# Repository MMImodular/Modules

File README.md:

# Modules
Repository for all my eurorack module designs

Each directory has its own ReadMe with information on each module

If you decide to get some of your own PCBs fabbed from these files, please consider shooting me a few bucks to help support future projects!

paypal.me/AboutBlank

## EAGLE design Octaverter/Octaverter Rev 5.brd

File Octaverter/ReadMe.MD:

# Octaverter

**Octaverter is currently in prototyping stages. The data here is to help beta testers with their builds. Nothing is guaranteed to work just yet.**

* 8 attenuverters in 12hp
* Each attenuverter is normalled to the one below it if no plug is inserted to its output
* Each input is normalled to 5V if no plug is inserted
* Each attenuverter has a gain of 1.5
* Bi-color LEDs to help visualize the output, red for negative, green for positive

Octaverter has been in the works for several months and has gone through a record number of revisions. This is 5th and hopefully last version of the module. Octaverter is a one-stop-shop for many functions beyond just attenuversion. It can be used as a mixer, offset generator, sidechain generator, amplifier, and even distortion.

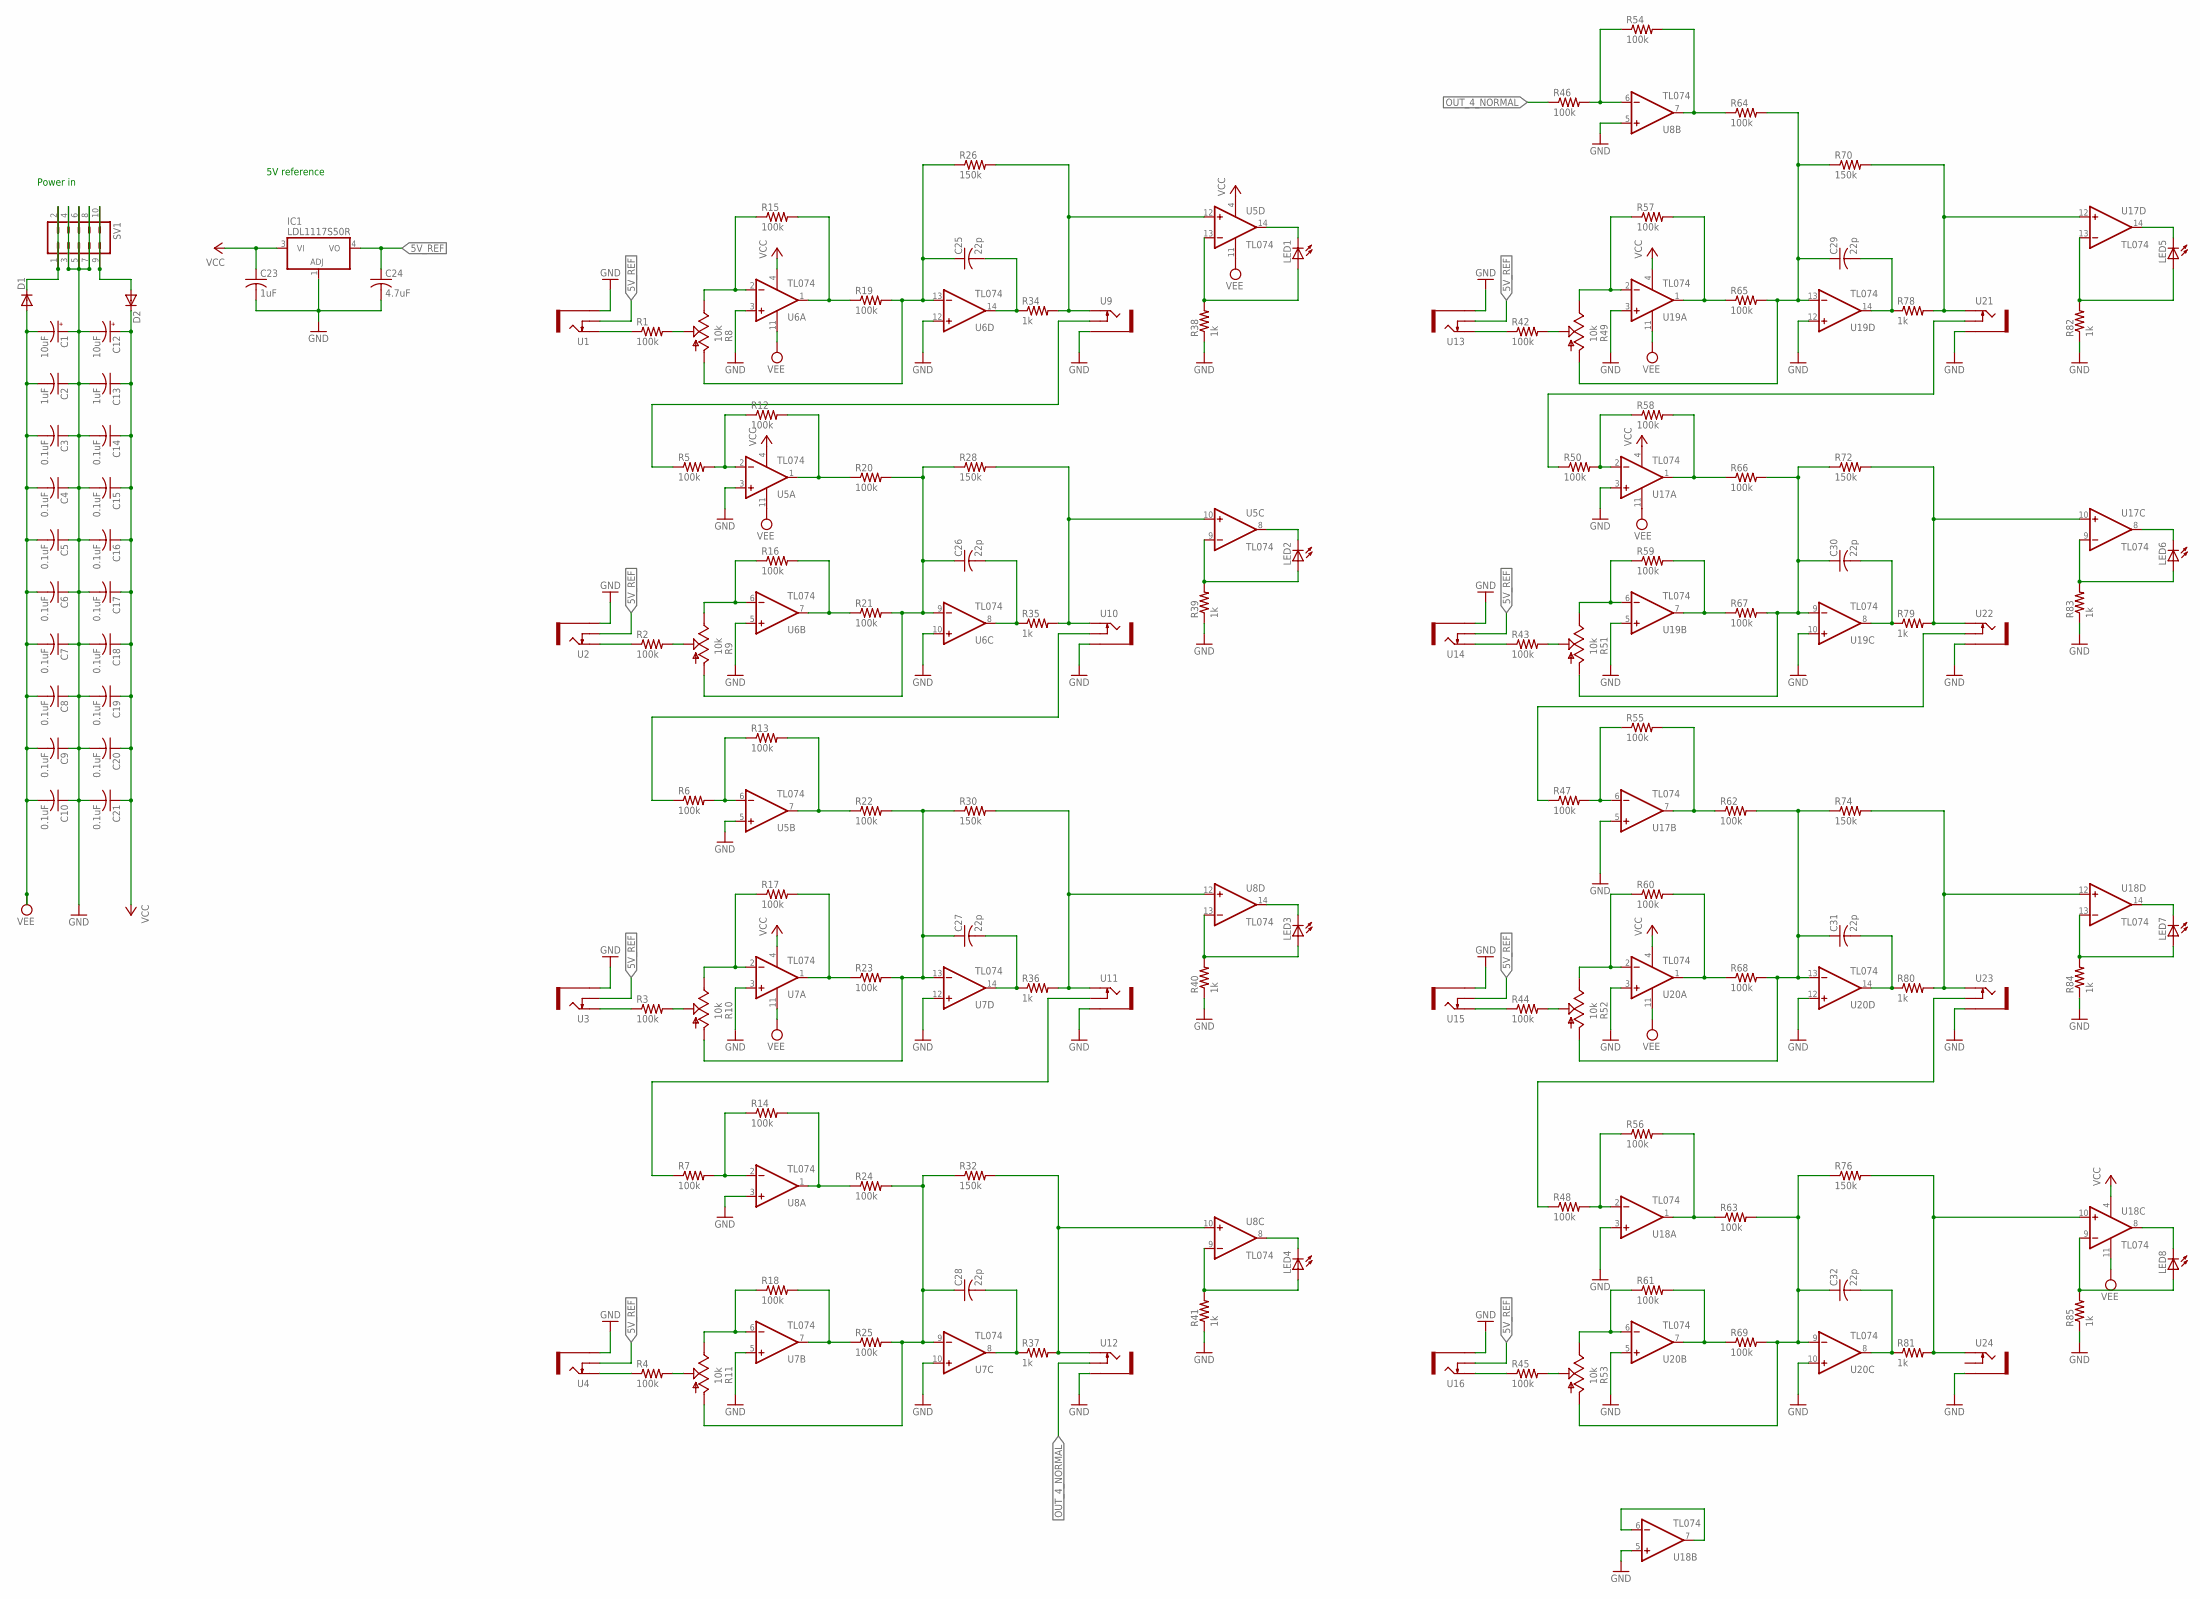
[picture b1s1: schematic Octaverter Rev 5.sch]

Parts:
C1, C12: 10uF; PANASONIC_B
C2, C13, C23: 1uF; C0603
C3, C4, C5, C6, C7, C8, C9, C10, C14, C15, C16, C17, C18, C19, C20, C21: 0.1uF; C0603
C24: 4.7uF; C0603
C25, C26, C27, C28, C29, C30, C31, C32: 22p; C0603
D1, D2: 1N5819HW; SOD123
IC1: LDL1117S50R; SOT223
LED1, LED2, LED3, LED4, LED5, LED6, LED7, LED8: LED3MM
R1, R2, R3, R4, R5, R6, R7, R12, R13, R14, R15, R16, R17, R18, R19, R20, R21, R22, R23, R24, R25, R42, R43, R44, R45, R46, R47, R48, R50, R54, R55, R56, R57, R58, R59, R60, R61, R62, R63, R64, R65, R66, R67, R68, R69: 100k; R0603
R8, R9, R10, R11, R49, R51, R52, R53: 10k; ALPS_POT_VERTICAL_PS
R26, R28, R30, R32, R70, R72, R74, R76: 150k; R0603
R34, R35, R36, R37, R38, R39, R40, R41, R78, R79, R80, R81, R82, R83, R84, R85: 1k; R0603
SV1: EURO_POWER_HEADERFAT_PADS; EURO_PWR_HEADER_FAT
U1, U2, U3, U4, U9, U10, U11, U12, U13, U14, U15, U16, U21, U22, U23, U24: THONKICONNNEW; WQP-PJ301M-12_JACK
U5, U6, U7, U8, U17, U18, U19, U20: TL074; SO14

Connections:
5V_REF: C24.1, IC1.4 (VO), U1.P$2_SWITCH (SWITCH), U2.P$2_SWITCH (SWITCH), U3.P$2_SWITCH (SWITCH), U4.P$2_SWITCH (SWITCH), U13.P$2_SWITCH (SWITCH), U14.P$2_SWITCH (SWITCH), U15.P$2_SWITCH (SWITCH), U16.P$2_SWITCH (SWITCH)
GND: C1.+, C2.1, C3.1, C4.1, C5.1, C6.1, C7.1, C8.1, C9.1, C10.1, C12.-, C13.2, C14.2, C15.2, C16.2, C17.2, C18.2, C19.2, C20.2, C21.2, C23.2, C24.2, IC1.1 (ADJ), R38.1, R39.1, R40.1, R41.1, R82.1, R83.1, R84.1, R85.1, SV1.3, SV1.4, SV1.5, SV1.6, SV1.7, SV1.8, U1.P$3_SLEEVE (SLEEVE), U2.P$3_SLEEVE (SLEEVE), U3.P$3_SLEEVE (SLEEVE), U4.P$3_SLEEVE (SLEEVE), U5.3 (+IN), U5.5 (+IN), U6.3 (+IN), U6.5 (+IN), U6.10 (+IN), U6.12 (+IN), U7.3 (+IN), U7.5 (+IN), U7.10 (+IN), U7.12 (+IN), U8.3 (+IN), U8.5 (+IN), U9.P$3_SLEEVE (SLEEVE), U10.P$3_SLEEVE (SLEEVE), U11.P$3_SLEEVE (SLEEVE), U12.P$3_SLEEVE (SLEEVE), U13.P$3_SLEEVE (SLEEVE), U14.P$3_SLEEVE (SLEEVE), U15.P$3_SLEEVE (SLEEVE), U16.P$3_SLEEVE (SLEEVE), U17.3 (+IN), U17.5 (+IN), U18.3 (+IN), U18.5 (+IN), U19.3 (+IN), U19.5 (+IN), U19.10 (+IN), U19.12 (+IN), U20.3 (+IN), U20.5 (+IN), U20.10 (+IN), U20.12 (+IN), U21.P$3_SLEEVE (SLEEVE), U22.P$3_SLEEVE (SLEEVE), U23.P$3_SLEEVE (SLEEVE), U24.P$3_SLEEVE (SLEEVE)
unnamed: R1.1, U1.P$1_TIP (TIP)
unnamed: R1.2, R8.P$2 (S)
unnamed: R8.P$1 (E), R15.1, U6.2 (-IN)
unnamed: R15.2, R19.1, U6.1 (OUT)
unnamed: C25.1, R8.P$3 (A), R19.2, R26.1, U6.13 (-IN)
unnamed: R2.1, U2.P$1_TIP (TIP)
unnamed: D1.C, SV1.1, SV1.2
unnamed: C25.2, R34.1, U6.14 (OUT)
unnamed: R26.2, R34.2, U5.12 (+IN), U9.P$1_TIP (TIP)
unnamed: R16.2, R21.1, U6.7 (OUT)
unnamed: R3.1, U3.P$1_TIP (TIP)
unnamed: R3.2, R10.P$2 (S)
unnamed: C26.2, R35.1, U6.8 (OUT)
unnamed: LED1.K (C), U5.14 (OUT)
unnamed: LED1.A, R38.2, U5.13 (-IN)
unnamed: R2.2, R9.P$2 (S)
unnamed: R9.P$1 (E), R16.1, U6.6 (-IN)
unnamed: R50.1, U21.P$2_SWITCH (SWITCH)
unnamed: R10.P$1 (E), R17.1, U7.2 (-IN)
unnamed: LED2.K (C), U5.8 (OUT)
unnamed: LED2.A, R39.2, U5.9 (-IN)
unnamed: D2.A, SV1.9, SV1.10
unnamed: R17.2, R23.1, U7.1 (OUT)
unnamed: C27.1, R10.P$3 (A), R22.2, R23.2, R30.1, U7.13 (-IN)
unnamed: C27.2, R36.1, U7.14 (OUT)
unnamed: U18.6 (-IN), U18.7 (OUT)
unnamed: R4.2, R11.P$2 (S)
unnamed: R11.P$1 (E), R18.1, U7.6 (-IN)
unnamed: C28.1, R11.P$3 (A), R24.2, R25.2, R32.1, U7.9 (-IN)
unnamed: R4.1, U4.P$1_TIP (TIP)
unnamed: R18.2, R25.1, U7.7 (OUT)
unnamed: C28.2, R37.1, U7.8 (OUT)
unnamed: LED3.K (C), U8.14 (OUT)
unnamed: LED3.A, R40.2, U8.13 (-IN)
unnamed: LED4.K (C), U8.8 (OUT)
unnamed: LED4.A, R41.2, U8.9 (-IN)
unnamed: R42.1, U13.P$1_TIP (TIP)
unnamed: R42.2, R49.P$2 (S)
unnamed: R49.P$1 (E), R57.1, U19.2 (-IN)
unnamed: R57.2, R65.1, U19.1 (OUT)
unnamed: C29.1, R49.P$3 (A), R64.2, R65.2, R70.1, U19.13 (-IN)
unnamed: C29.2, R78.1, U19.14 (OUT)
unnamed: LED5.K (C), U17.14 (OUT)
unnamed: LED5.A, R82.2, U17.13 (-IN)
unnamed: R43.2, R51.P$2 (S)
unnamed: R51.P$1 (E), R59.1, U19.6 (-IN)
unnamed: C30.1, R51.P$3 (A), R66.2, R67.2, R72.1, U19.9 (-IN)
unnamed: R43.1, U14.P$1_TIP (TIP)
unnamed: R59.2, R67.1, U19.7 (OUT)
unnamed: C30.2, R79.1, U19.8 (OUT)
unnamed: LED6.K (C), U17.8 (OUT)
unnamed: LED6.A, R83.2, U17.9 (-IN)
unnamed: R44.1, U15.P$1_TIP (TIP)
unnamed: R44.2, R52.P$2 (S)
unnamed: R52.P$1 (E), R60.1, U20.2 (-IN)
unnamed: R60.2, R68.1, U20.1 (OUT)
unnamed: C31.1, R52.P$3 (A), R62.2, R68.2, R74.1, U20.13 (-IN)
unnamed: C31.2, R80.1, U20.14 (OUT)
unnamed: R45.2, R53.P$2 (S)
unnamed: R53.P$1 (E), R61.1, U20.6 (-IN)
unnamed: C32.1, R53.P$3 (A), R63.2, R69.2, R76.1, U20.9 (-IN)
unnamed: R45.1, U16.P$1_TIP (TIP)
unnamed: R61.2, R69.1, U20.7 (OUT)
unnamed: C32.2, R81.1, U20.8 (OUT)
unnamed: LED7.A, R84.2, U18.13 (-IN)
unnamed: LED8.A, R85.2, U18.9 (-IN)
unnamed: LED7.K (C), U18.14 (OUT)
unnamed: LED8.K (C), U18.8 (OUT)
unnamed: R5.1, U9.P$2_SWITCH (SWITCH)
unnamed: R5.2, R12.1, U5.2 (-IN)
unnamed: C26.1, R9.P$3 (A), R20.2, R21.2, R28.1, U6.9 (-IN)
unnamed: R12.2, R20.1, U5.1 (OUT)
unnamed: R6.1, U10.P$2_SWITCH (SWITCH)
unnamed: R6.2, R13.1, U5.6 (-IN)
unnamed: R13.2, R22.1, U5.7 (OUT)
unnamed: R50.2, R58.1, U17.2 (-IN)
unnamed: R7.1, U11.P$2_SWITCH (SWITCH)
unnamed: R7.2, R14.1, U8.2 (-IN)
unnamed: R14.2, R24.1, U8.1 (OUT)
unnamed: R58.2, R66.1, U17.1 (OUT)
unnamed: R47.1, U22.P$2_SWITCH (SWITCH)
unnamed: R47.2, R55.1, U17.6 (-IN)
unnamed: R55.2, R62.1, U17.7 (OUT)
unnamed: R48.1, U23.P$2_SWITCH (SWITCH)
unnamed: R48.2, R56.1, U18.2 (-IN)
unnamed: R56.2, R63.1, U18.1 (OUT)
unnamed: R46.2, R54.1, U8.6 (-IN)
unnamed: R54.2, R64.1, U8.7 (OUT)
unnamed: R30.2, R36.2, U8.12 (+IN), U11.P$1_TIP (TIP)
unnamed: R32.2, R37.2, U8.10 (+IN), U12.P$1_TIP (TIP)
unnamed: R76.2, R81.2, U18.10 (+IN), U24.P$1_TIP (TIP)
unnamed: R28.2, R35.2, U5.10 (+IN), U10.P$1_TIP (TIP)
unnamed: R74.2, R80.2, U18.12 (+IN), U23.P$1_TIP (TIP)
unnamed: R72.2, R79.2, U17.10 (+IN), U22.P$1_TIP (TIP)
unnamed: R70.2, R78.2, U17.12 (+IN), U21.P$1_TIP (TIP)
OUT_4_NORMAL: R46.1, U12.P$2_SWITCH (SWITCH)
VCC: C12.+, C13.1, C14.1, C15.1, C16.1, C17.1, C18.1, C19.1, C20.1, C21.1, C23.1, D2.C, IC1.3 (VI), U5.4 (V+), U6.4 (V+), U7.4 (V+), U8.4 (V+), U17.4 (V+), U18.4 (V+), U19.4 (V+), U20.4 (V+)
VEE: C1.-, C2.2, C3.2, C4.2, C5.2, C6.2, C7.2, C8.2, C9.2, C10.2, D1.A, U5.11 (V-), U6.11 (V-), U7.11 (V-), U8.11 (V-), U17.11 (V-), U18.11 (V-), U19.11 (V-), U20.11 (V-)

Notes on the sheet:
Power in
5V reference

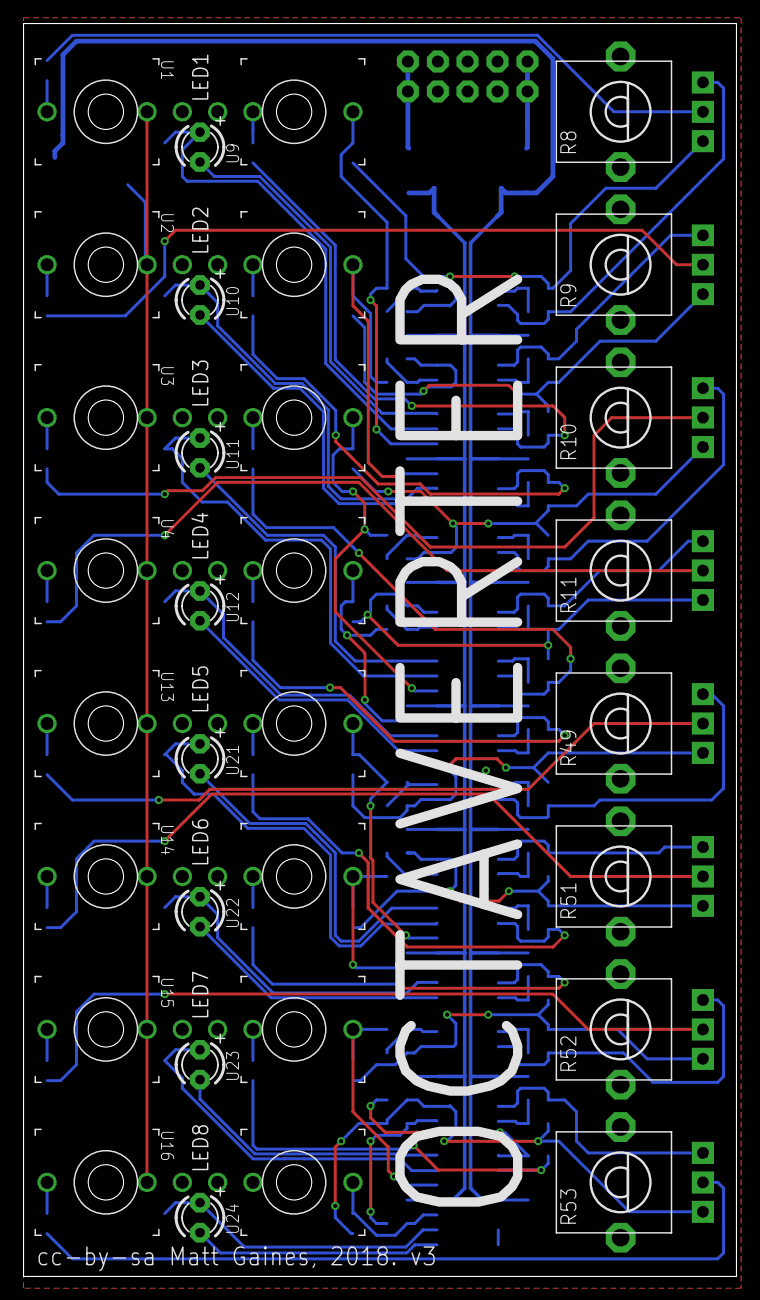
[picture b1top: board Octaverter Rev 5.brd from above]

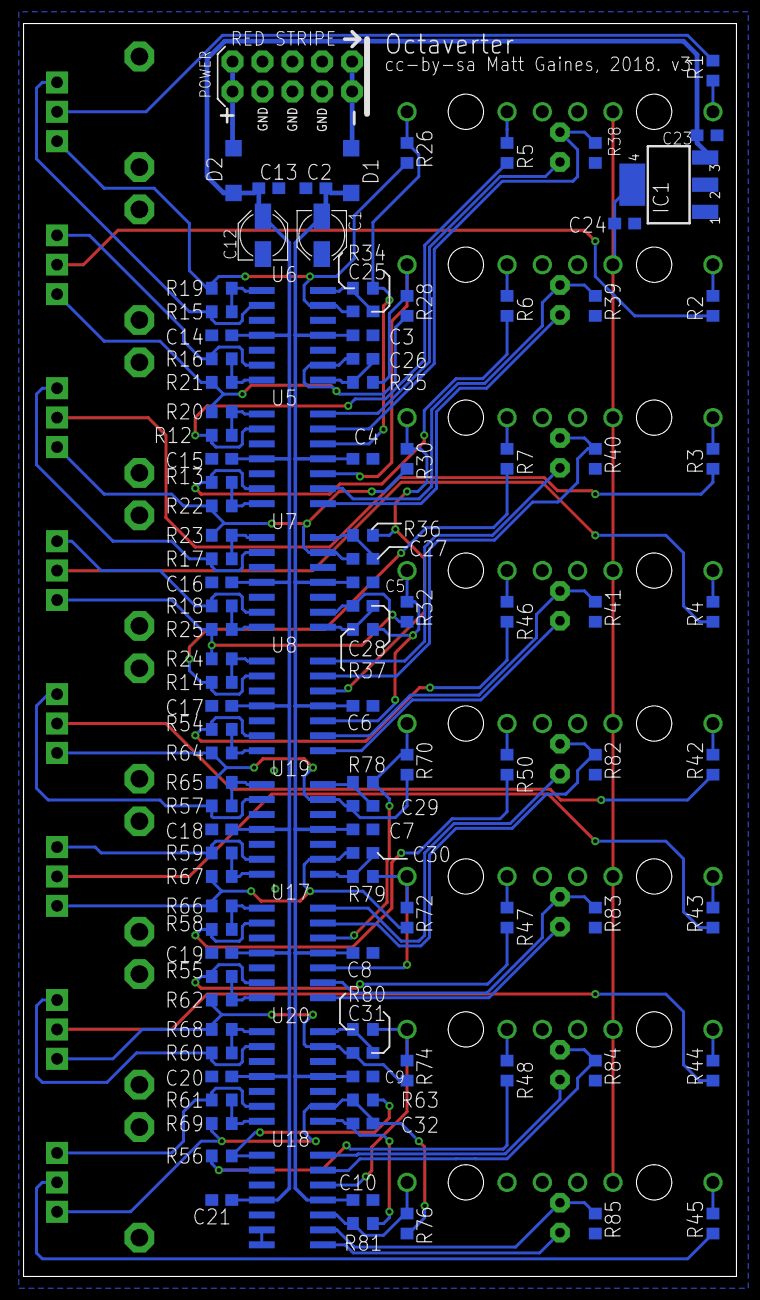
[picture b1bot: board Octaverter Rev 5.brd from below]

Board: 2 copper layers, 60.6 x 106.5 mm, 143 parts (111 on the bottom side), 100 nets.

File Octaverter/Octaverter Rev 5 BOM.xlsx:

Qty | Value | Device | Package | Parts | Description | Column1 | _1
1 |  | EURO_POWER_HEADERFAT_PADS | EURO_PWR_HEADER_FAT | SV1 | Power Header
8 |  | LED3MM | LED3MM | LED1, LED2, LED3, LED4, LED5, LED6, LED7, LED8 | LED
16 | 0.1uF | C-USC0603 | C0603 | C3, C4, C5, C6, C7, C8, C9, C10, C14, C15, C16, C17, C18, C19, C20, C21 | CAPACITOR, American symbol
45 | 100k | R-US_R0603 | R0603 | R1, R2, R3, R4, R5, R6, R7, R12, R13, R14, R15, R16, R17, R18, R19, R20, R21, R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 | RESISTOR, American symbol
8 | 10k | POT_USVERTICAL_PS | ALPS_POT_VERTICAL_PS | R8, R9, R10, R11, R49, R51, R52, R53 | Potentiometer, Alpha Style
2 | 10uF | CPOL-USB | PANASONIC_B | C1, C12 | POLARIZED CAPACITOR, American symbol
8 | 150k | R-US_R0603 | R0603 | R26, R28, R30, R32, R70, R72, R74, R76 | RESISTOR, American symbol
2 | 1N5819HW | DIODE-SOD123 | SOD123 | D1, D2 | DIODE
16 | 1k | R-US_R0603 | R0603 | R34, R35, R36, R37, R38, R39, R40, R41, R78, R79, R80, R81, R82, R83, R84, R85 | RESISTOR, American symbol
3 | 1uF | C-USC0603 | C0603 | C2, C13, C23 | CAPACITOR, American symbol
8 | 22p | C-USC0603 | C0603 | C25, C26, C27, C28, C29, C30, C31, C32 | CAPACITOR, American symbol
1 | 4.7uF | C-USC0603 | C0603 | C24 | CAPACITOR, American symbol
1 | LDL1117S50R | 317EMP | SOT223 | IC1 | Positive VOLTAGE REGULATOR
16 | THONKICONNNEW | THONKICONNNEW | WQP-PJ301M-12_JACK | U1, U2, U3, U4, U9, U10, U11, U12, U13, U14, U15, U16, U21, U22, U23, U24 | 3.5mm socket for Eurorack modular synths
8 | TL074 | TL074_SMD | SO14 | U5, U6, U7, U8, U17, U18, U19, U20 | Generic Quad Op Amp

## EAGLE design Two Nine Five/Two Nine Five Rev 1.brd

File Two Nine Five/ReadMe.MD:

**If you would like to build this project yourself, PCBs can be purchased through [Pusherman](https://pushermanproductions.com/product/mmi-modular-two-nine-five-buchla-comb-filter-pcb-14hp-black-gold-aluminium-panel/) or [Modular Addict](https://modularaddict.com/mmi-259-pcbpanel)**

**If you would like to purchase a pre-built unit, keep an eye on my [Reverb shop](https://reverb.com/shop/mmi-modular)**

# Two Nine Five

* Eurorack adaptation of the Buchla Model 295 10-channel comb filter
* 10 LED sliders control the amplitude of each band sent through the SUM output
* Individual channel outputs to the right of each slider
* Tunable band frequencies, Q's, and amplitude via trim pots on the back of the module.

This recreation of the Model 295 has been in my head since before I owned any modular. After using a restored Buchla at the Oberlin Conservatory of Music, the 295 became one of my favorite modules in the whole case. Buchla modular is far out of my budget so with the original schematics in hand, I made a much more compact 3U version of it. The circuitry is exactly the same, though more modern op-amps have to be used since the ones used in the original design are no longer available.

---

**Things to note when building**

It is absolutely imperative that you solder R13, R39, R17, R37, R19, R35, R25, and R33 properly before mounting the trim pots as they will be very difficult to reach once all components are in place. To confirm they are soldered properly, measure the resistance between the two middle pins of each trim pot location. For instance, the resistance between the middle pin of VR10 and VR9 should be roughly 68 kOhms.

In addition, please heed the warning on the front of the PCB and place the trim pots on the back of the module. There is not enough space between the PCB and panel for the trim pots and having them on the back allows for you to tune everything without taking the panel off. I kept the silk screen for the pots on the top side in order to avoid cluttering the bottom silkscreen layer.

As for the illuminated slide pots, there's a few things to consider. They are acting as cross faders so any value between 10k and 100k should work just fine. They are taking an audio signal so ideally you want audio response, but linear response will function just fine. Ideal shaft length is 15mm but I have used 10mm successfully, the tops are just a tad close to the panel. You do not want a center detent if you can help it. The sliders I used can be found on Mouser: 652-PTL20-10R0-103B2

---

**How to tune your 295**

Note: You may want to keep the volume down for this or else you might give yourself a headache.

*Tuning Frequency*

* Turn each 20k trim pot so that every band has maximum gain (some bands will self-oscillate, others will not)
* Patch white noise to **IN** and monitor **SUM** with a FFT-capable spectrum analyzer or parametric/graphic EQ
* Slide the potentiometer of the band you want to tune all the way to the right
* Turn the appropriate 100k trim pot until the peak is centered on the desired frequency
* Repeat for each band

*Tuning Gain/Q*

* Using a sine wave oscillator, patch the wave directly to your output 
* Set the gain between your modular and a VU meter (usually within a DAW) so that the output is now at 0dB
* Leaving the output gain unchanged, move the sine wave to an attenuator and attenuate it down to -6.5dB
* Patch this attenuated sine wave to **IN** then patch **SUM** to your output
* Slide the potentiometer of the band you want to tune all the way to the right
* Tune your sine wave to match the frequency of the band you would like to tune
* Turn the appropriate 20k trim pot until your output is at 0dB
* Repeat for each band

It may help to monitor your output with an oscilloscope to see how your output clips. Note that each band clips asymmetrically. This can cause some interesting harmonics to show up so feel free to tune your filter to taste, no need to follow this guide to a T.

---

PCB and panel designed by me

Original schematic by Don Buchla

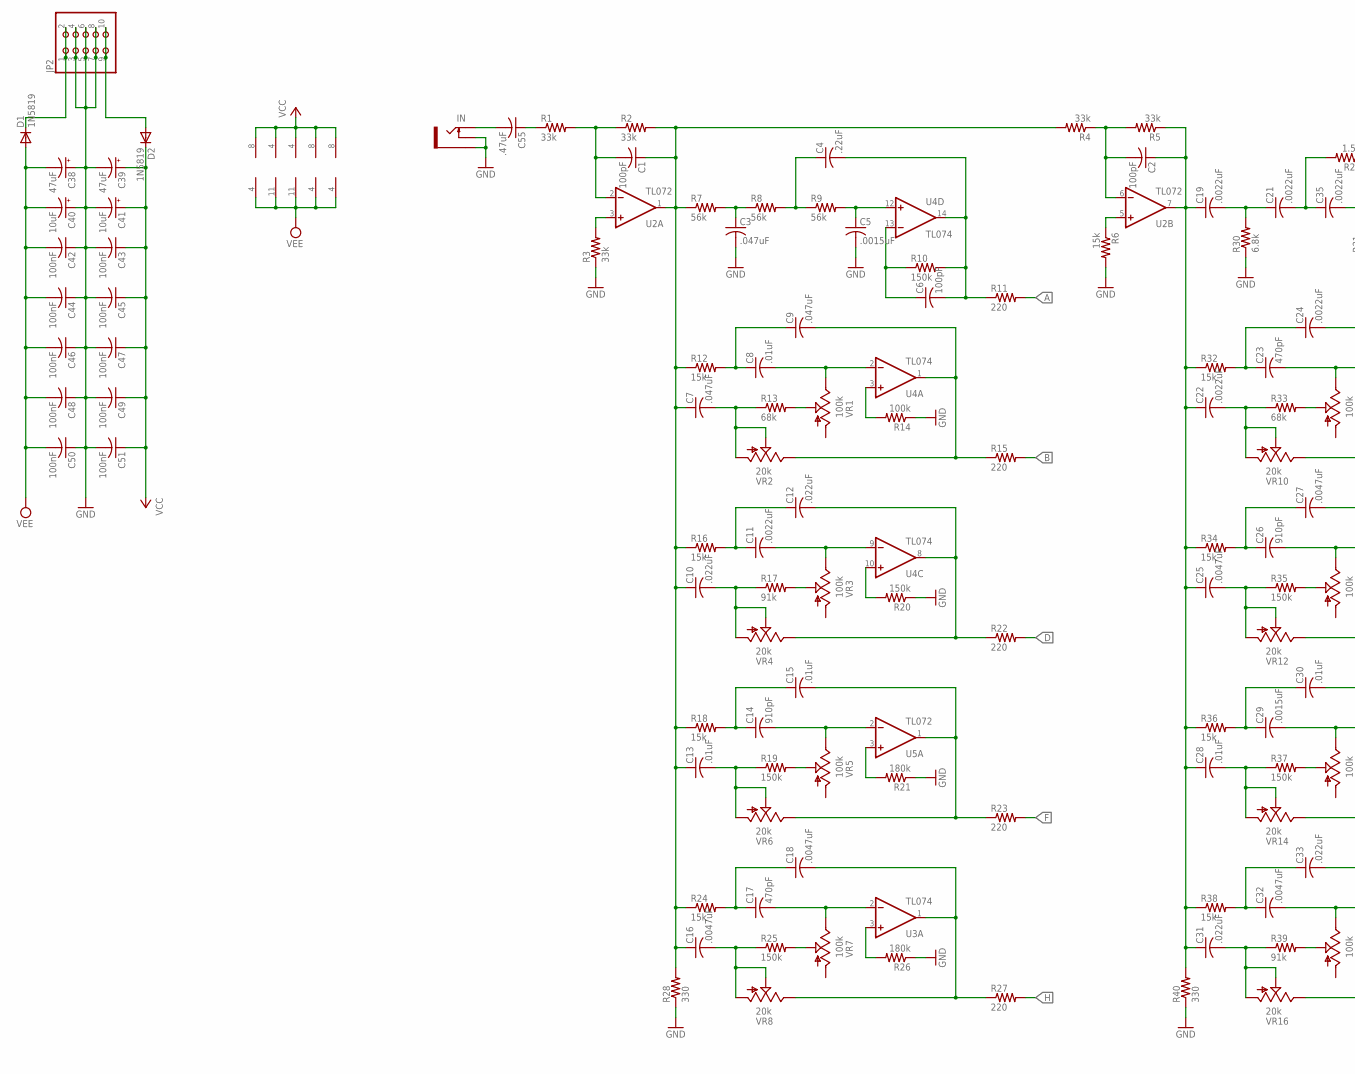
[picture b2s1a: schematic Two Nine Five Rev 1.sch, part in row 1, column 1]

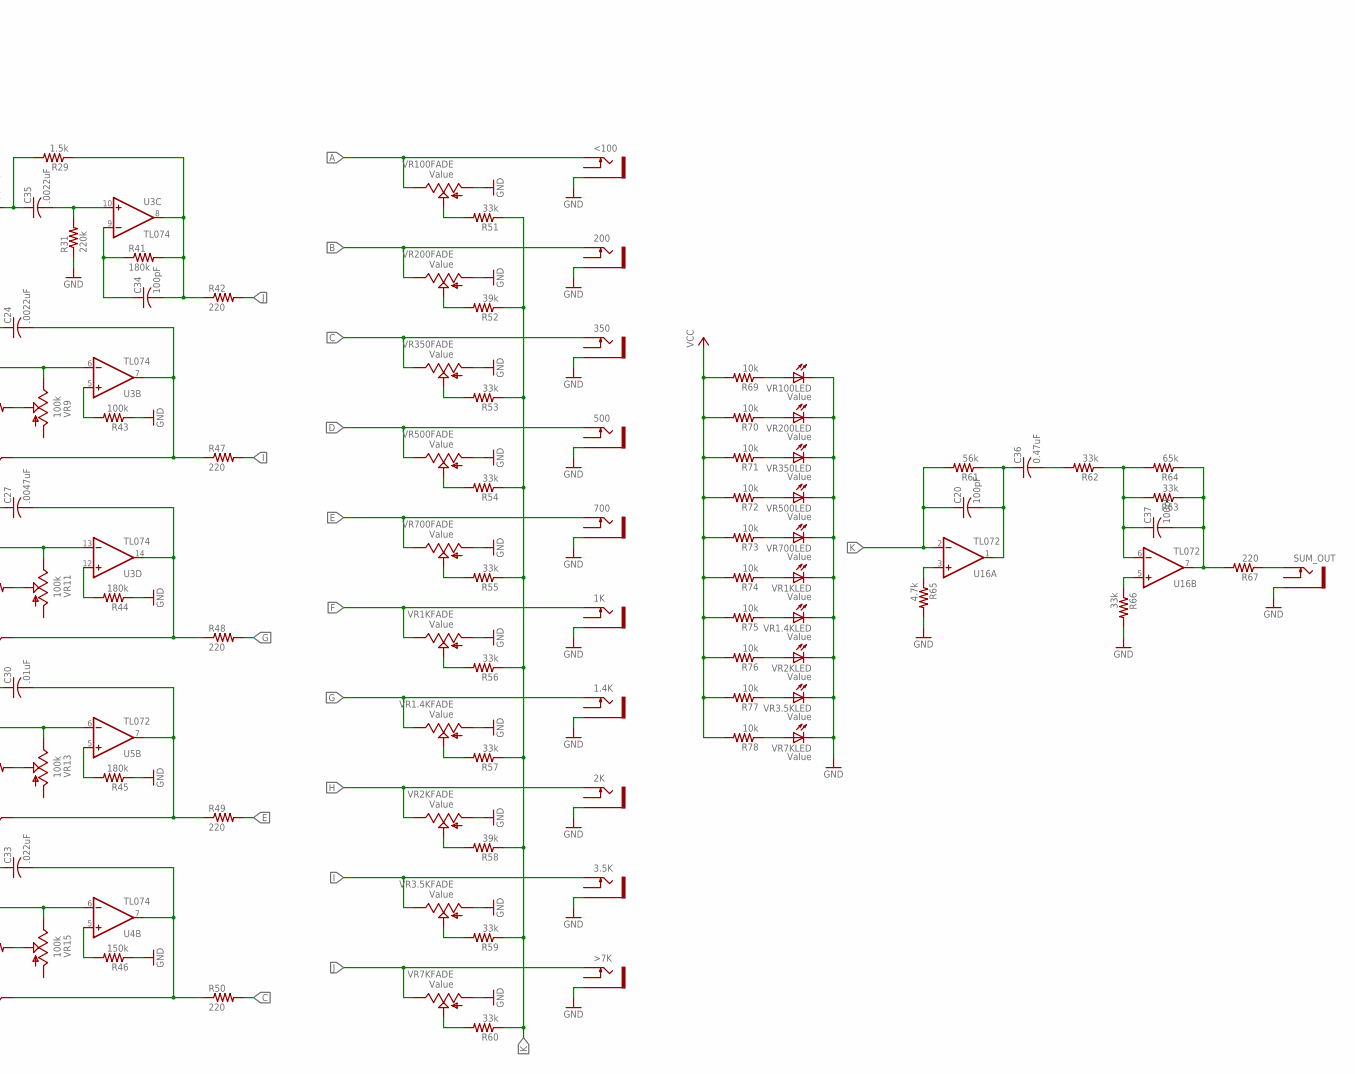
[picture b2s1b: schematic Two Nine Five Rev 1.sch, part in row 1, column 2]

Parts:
1.4K, 1K, 2K, 3.5K, 200, 350, 500, 700: THONKICONNNEW; WQP-PJ301M-12_JACK
<100: THONKICONNNEW; WQP-PJ301M-12_JACK
>7K: THONKICONNNEW; WQP-PJ301M-12_JACK
C1, C2, C6, C20, C34, C37: 100pF; C0603
C3, C7, C9: .047uF; C0603
C4: .22uF; C0603
C5, C29: .0015uF; C0603
C8, C13, C15, C28, C30: .01uF; C0603
C10, C12, C31, C33: .022uF; C0603
C11, C19, C21, C22, C24, C35: .0022uF; C0603
C14, C26: 910pF; C0603
C16, C18, C25, C27, C32: .0047uF; C0603
C17, C23: 470pF; C0603
C36: 0.47uF; C0603
C38, C39: 47uF; PANASONIC_D
C40, C41: 10uF; PANASONIC_B
C42, C43, C44, C45, C46, C47, C48, C49, C50, C51: 100nF; C0603
C55: .47uF; C0603
D1, D2: 1N5819; SOD123
IN: THONKICONNNEW; WQP-PJ301M-12_JACK
JP2: PINHD-2X5SMT; 2X05_SMT
R1, R2, R3, R4, R5, R51, R53, R54, R55, R56, R57, R59, R60, R62, R63, R66: 33k; R0603
R6, R12, R16, R18, R24, R32, R34, R36, R38: 15k; R0603
R7, R8, R9, R61: 56k; R0603
R10, R19, R20, R25, R35, R37, R46: 150k; R0603
R11, R15, R22, R23, R27, R42, R47, R48, R49, R50, R67: 220; R0603
R13, R33: 68k; R0603
R14, R43: 100k; R0603
R17, R39: 91k; R0603
R21, R26, R41, R44, R45: 180k; R0603
R28, R40: 330; R0603
R29: 1.5k; R0603
R30: 6.8k; R0603
R31: 220k; R0603
R52, R58: 39k; R0603
R64: 65k; R0603
R65: 4.7k; R0603
R69, R70, R71, R72, R73, R74, R75, R76, R77, R78: 10k; R0603
SUM_OUT: THONKICONNNEW; WQP-PJ301M-12_JACK
U2, U5, U16: TL072; SO08
U3, U4: TL074; SO14
VR1, VR3, VR5, VR7, VR9, VR11, VR13, VR15: 100k; RJ9W
VR1.4K, VR1K, VR2K, VR3.5K, VR7K, VR100, VR200, VR350, VR500, VR700: Value; ALPHA_ILL_FADER_20MM_REV2
VR2, VR4, VR6, VR8, VR10, VR12, VR14, VR16: 20k; RJ9W

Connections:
A: <100.P$1_TIP (TIP), R11.2, VR100.1 (E)
B: 200.P$1_TIP (TIP), R15.2, VR200.1 (E)
C: 350.P$1_TIP (TIP), R50.2, VR350.1 (E)
D: 500.P$1_TIP (TIP), R22.2, VR500.1 (E)
E: 700.P$1_TIP (TIP), R49.2, VR700.1 (E)
F: 1K.P$1_TIP (TIP), R23.2, VR1K.1 (E)
G: 1.4K.P$1_TIP (TIP), R48.2, VR1.4K.1 (E)
GND: 1.4K.P$3_SLEEVE (SLEEVE), 1K.P$3_SLEEVE (SLEEVE), 2K.P$3_SLEEVE (SLEEVE), 3.5K.P$3_SLEEVE (SLEEVE), 200.P$3_SLEEVE (SLEEVE), 350.P$3_SLEEVE (SLEEVE), 500.P$3_SLEEVE (SLEEVE), 700.P$3_SLEEVE (SLEEVE), <100.P$3_SLEEVE (SLEEVE), >7K.P$3_SLEEVE (SLEEVE), C3.2, C5.2, C38.+, C39.-, C40.+, C41.-, C42.1, C43.2, C44.1, C45.2, C46.1, C47.2, C48.1, C49.2, C50.1, C51.2, IN.P$2_SWITCH (SWITCH), IN.P$3_SLEEVE (SLEEVE), JP2.3, JP2.4, JP2.5, JP2.6, JP2.7, JP2.8, R3.1, R6.2, R14.1, R20.1, R21.1, R26.1, R28.1, R30.1, R31.1, R40.1, R43.1, R44.1, R45.1, R46.1, R65.2, R66.2, SUM_OUT.P$3_SLEEVE (SLEEVE), VR1.4K.3 (A), VR1.4K.E (C), VR1K.3 (A), VR1K.E (C), VR2K.3 (A), VR2K.E (C), VR3.5K.3 (A), VR3.5K.E (C), VR7K.3 (A), VR7K.E (C), VR100.3 (A), VR100.E (C), VR200.3 (A), VR200.E (C), VR350.3 (A), VR350.E (C), VR500.3 (A), VR500.E (C), VR700.3 (A), VR700.E (C)
H: 2K.P$1_TIP (TIP), R27.2, VR2K.1 (E)
I: 3.5K.P$1_TIP (TIP), R47.2, VR3.5K.1 (E)
J: >7K.P$1_TIP (TIP), R42.2, VR7K.1 (E)
K: C20.1, R51.1, R52.1, R53.1, R54.1, R55.1, R56.1, R57.1, R58.1, R59.1, R60.1, R61.2, U16.2 (-IN)
unnamed: C55.2, IN.P$1_TIP (TIP)
unnamed: C1.2, R1.2, R2.1, U2.2 (-IN)
unnamed: C1.1, C7.1, C10.1, C13.1, C16.1, R2.2, R4.2, R7.1, R12.1, R16.1, R18.1, R24.1, R28.2, U2.1 (OUT)
unnamed: R3.2, U2.3 (+IN)
unnamed: C3.1, R7.2, R8.1
unnamed: C2.2, R4.1, R5.2, U2.6 (-IN)
unnamed: C2.1, C19.1, C22.1, C25.1, C28.1, C31.1, R5.1, R32.1, R34.1, R36.1, R38.1, R40.2, U2.7 (OUT)
unnamed: R6.1, U2.5 (+IN)
unnamed: C4.1, R8.2, R9.1
unnamed: C5.1, R9.2, U4.12 (+IN)
unnamed: C4.2, C6.2, R10.2, R11.1, U4.14 (OUT)
unnamed: C6.1, R10.1, U4.13 (-IN)
unnamed: C8.1, C9.1, R12.2
unnamed: C7.2, R13.1, VR2.A, VR2.S
unnamed: R13.2, VR1.S
unnamed: C8.2, U4.2 (-IN), VR1.E
unnamed: R14.2, U4.3 (+IN)
unnamed: C9.2, R15.1, U4.1 (OUT), VR2.E
unnamed: R26.2, U3.3 (+IN)
unnamed: C11.1, C12.1, R16.2
unnamed: C10.2, R17.1, VR4.A, VR4.S
unnamed: R17.2, VR3.S
unnamed: C11.2, U4.9 (-IN), VR3.E
unnamed: C12.2, R22.1, U4.8 (OUT), VR4.E
unnamed: C17.1, C18.1, R24.2
unnamed: C14.1, C15.1, R18.2
unnamed: C13.2, R19.1, VR6.A, VR6.S
unnamed: R19.2, VR5.S
unnamed: C14.2, U5.2 (-IN), VR5.E
unnamed: C15.2, R23.1, U5.1 (OUT), VR6.E
unnamed: R20.2, U4.10 (+IN)
unnamed: R21.2, U5.3 (+IN)
unnamed: C16.2, R25.1, VR8.A, VR8.S
unnamed: R25.2, VR7.S
unnamed: C17.2, U3.2 (-IN), VR7.E
unnamed: C18.2, R27.1, U3.1 (OUT), VR8.E
unnamed: C19.2, C21.1, R30.2
unnamed: C35.2, R31.2, U3.10 (+IN)
unnamed: C21.2, C35.1, R29.2
unnamed: R65.1, U16.3 (+IN)
unnamed: C34.2, R29.1, R41.2, R42.1, U3.8 (OUT)
unnamed: C23.1, C24.1, R32.2
unnamed: C22.2, R33.1, VR10.A, VR10.S
unnamed: R39.2, VR15.S
unnamed: C23.2, U3.6 (-IN), VR9.E
unnamed: C24.2, R47.1, U3.7 (OUT), VR10.E
unnamed: C26.1, C27.1, R34.2
unnamed: C25.2, R35.1, VR12.A, VR12.S
unnamed: R37.2, VR13.S
unnamed: C26.2, U3.13 (-IN), VR11.E
unnamed: C27.2, R48.1, U3.14 (OUT), VR12.E
unnamed: C29.1, C30.1, R36.2
unnamed: C28.2, R37.1, VR14.A, VR14.S
unnamed: R35.2, VR11.S
unnamed: C29.2, U5.6 (-IN), VR13.E
unnamed: C30.2, R49.1, U5.7 (OUT), VR14.E
unnamed: C32.1, C33.1, R38.2
unnamed: C31.2, R39.1, VR16.A, VR16.S
unnamed: R33.2, VR9.S
unnamed: C32.2, U4.6 (-IN), VR15.E
unnamed: C33.2, R50.1, U4.7 (OUT), VR16.E
unnamed: R51.2, VR100.2 (S)
unnamed: C34.1, R41.1, U3.9 (-IN)
unnamed: R43.2, U3.5 (+IN)
unnamed: R44.2, U3.12 (+IN)
unnamed: R45.2, U5.5 (+IN)
unnamed: R46.2, U4.5 (+IN)
unnamed: R66.1, U16.5 (+IN)
unnamed: R52.2, VR200.2 (S)
unnamed: C20.2, C36.1, R61.1, U16.1 (OUT)
unnamed: R53.2, VR350.2 (S)
unnamed: C36.2, R62.2
unnamed: R54.2, VR500.2 (S)
unnamed: C37.1, R62.1, R63.2, R64.2, U16.6 (-IN)
unnamed: R55.2, VR700.2 (S)
unnamed: C37.2, R63.1, R64.1, R67.2, U16.7 (OUT)
unnamed: R56.2, VR1K.2 (S)
unnamed: R67.1, SUM_OUT.P$1_TIP (TIP)
unnamed: R57.2, VR1.4K.2 (S)
unnamed: D2.A, JP2.9, JP2.10
unnamed: R58.2, VR2K.2 (S)
unnamed: R69.1, VR100.B (A)
unnamed: R59.2, VR3.5K.2 (S)
unnamed: D1.C, JP2.1, JP2.2
unnamed: R60.2, VR7K.2 (S)
unnamed: R70.1, VR200.B (A)
unnamed: R71.1, VR350.B (A)
unnamed: R72.1, VR500.B (A)
unnamed: R73.1, VR700.B (A)
unnamed: R74.1, VR1K.B (A)
unnamed: R75.1, VR1.4K.B (A)
unnamed: R76.1, VR2K.B (A)
unnamed: R77.1, VR3.5K.B (A)
unnamed: R78.1, VR7K.B (A)
unnamed: C55.1, R1.1
VCC: C39.+, C41.+, C43.1, C45.1, C47.1, C49.1, C51.1, D2.C, R69.2, R70.2, R71.2, R72.2, R73.2, R74.2, R75.2, R76.2, R77.2, R78.2, U2.8 (V+), U3.4 (V+), U4.4 (V+), U5.8 (V+), U16.8 (V+)
VEE: C38.-, C40.-, C42.2, C44.2, C46.2, C48.2, C50.2, D1.A, U2.4 (V-), U3.11 (V-), U4.11 (V-), U5.4 (V-), U16.4 (V-)

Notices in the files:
Cirrus/Cirrus.brd:
cc-by-sa Olivier Gillet, 2015. v3
DDB Power Supply/DDB Power Supply.brd:
CC-BY-SA: Matt Gaines
Octaverter/Octaverter Rev 5.brd:
cc-by-sa Matt Gaines, 2018. v3
parts and their libraries:
SparkFun-Connectors: Licensing: Creative Commons ShareAlike 4.0 International - https://creativecommons.org/licenses/by-sa/4.0
